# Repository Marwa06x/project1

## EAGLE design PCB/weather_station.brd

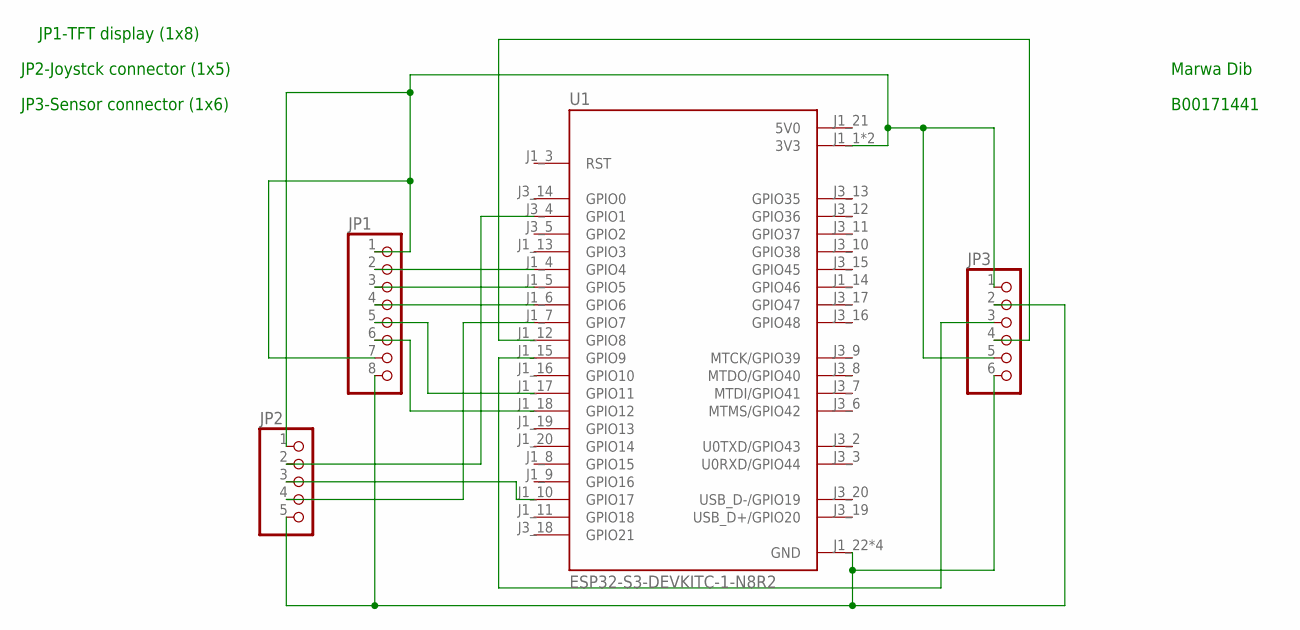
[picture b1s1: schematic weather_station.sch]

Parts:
JP1: PINHD-1X8; 1X08
JP2: PINHD-1X5; 1X05
JP3: PINHD-1X6; 1X06
U1: ESP32-S3-DEVKITC-1-N8R2; XCVR_ESP32-S3-DEVKITC-1-N8R2

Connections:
5V0: U1.J1_21 (5V0)
J_TFT: JP1.3, U1.J1_5 (GPIO5)
unnamed: JP1.2, U1.J1_4 (GPIO4)
unnamed: JP1.4, U1.J1_6 (GPIO6)
unnamed: JP1.5, U1.J1_17 (GPIO11)
unnamed: JP3.3, U1.J1_15 (GPIO9)
unnamed: JP1.8, JP2.5, JP3.2, JP3.6, U1.J1_22 (GND), U1.J3_1 (GND), U1.J3_21 (GND), U1.J3_22 (GND)
unnamed: JP1.1, JP1.7, JP2.1, JP3.1, JP3.5, U1.J1_1 (3V3), U1.J1_2 (3V3)
unnamed: JP2.3, U1.J1_10 (GPIO17)
unnamed: JP2.4, U1.J1_7 (GPIO7)
unnamed: JP1.6, U1.J1_18 (GPIO12)
unnamed: JP2.2, U1.J3_4 (GPIO1)
unnamed: JP3.4, U1.J1_12 (GPIO8)

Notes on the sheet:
Marwa Dib
B00171441
JP1-TFT display (1x8)
JP2-Joystck connector (1x5)
JP3-Sensor connector (1x6)

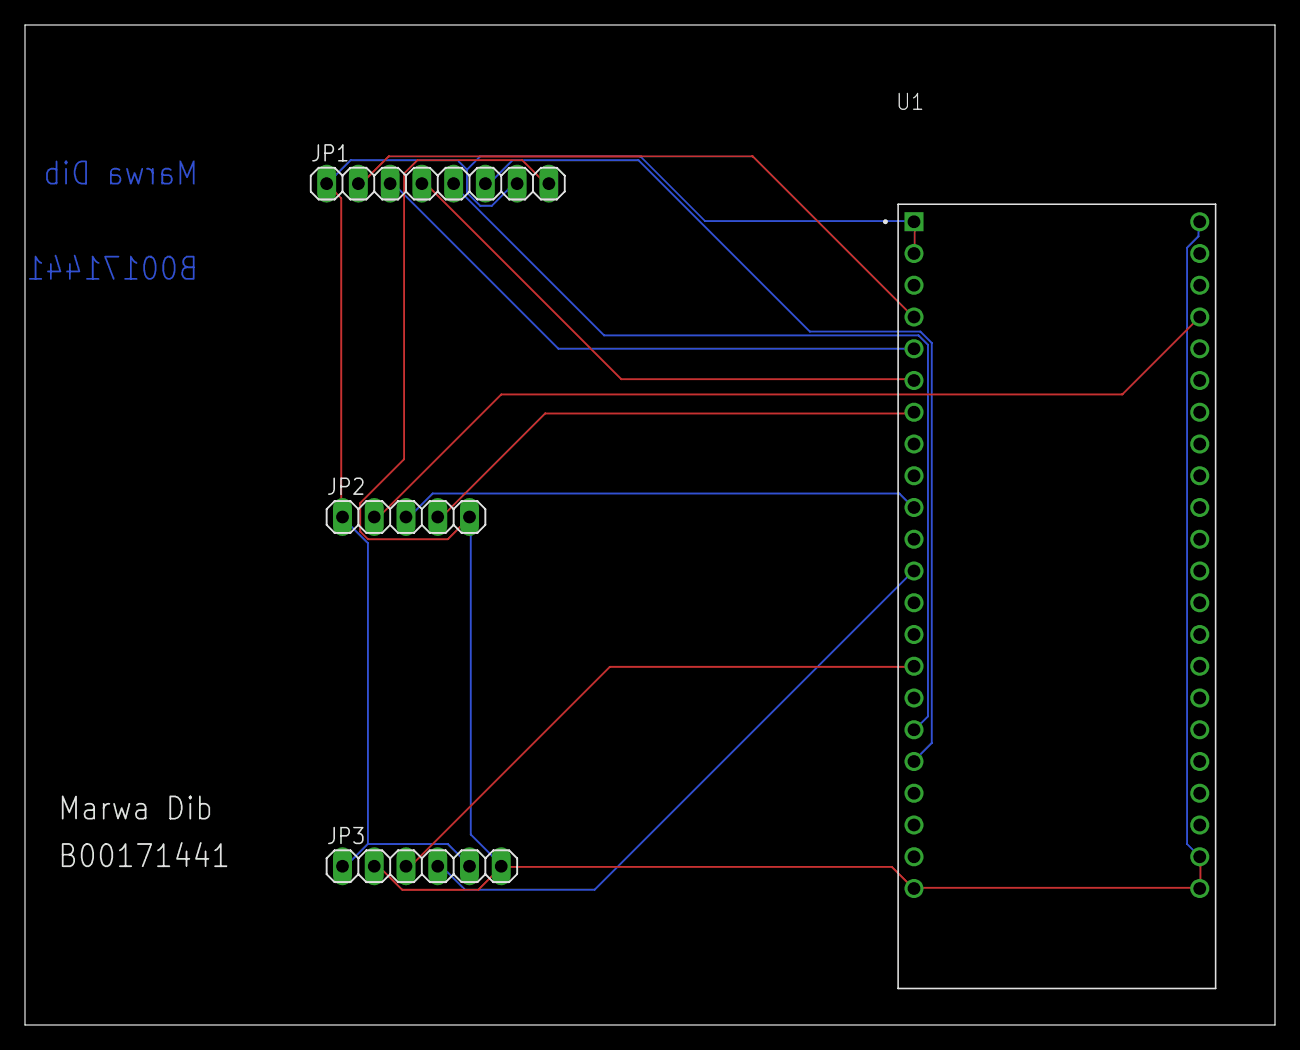
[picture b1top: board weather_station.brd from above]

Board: 2 copper layers, 100.0 x 80.0 mm, 4 parts (0 on the bottom side), 12 nets.
